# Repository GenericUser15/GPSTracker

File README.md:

# GPS Tracker

After having to cancel vet appointments because my cats were gallivanting somewhere outside, I decided to build a GPS tracking collar. These already exist but I wanted to create a fully open sourced version. I'm an embedded software engineer so my PCB knowledge is lacking, I'm much more software orientated! The PCB has been designed on KiCad.

# Architecture

The device uses a U-BLOX SARA-N310 LTE module, U-BLOX ZOE-M8G GPS module, an embedded SIM card and an STM32L011 to control everything.

The ST uses two UART lines to communicate with the GPS device and the LTE device. The GPS device will output NMEA messages by default but both lines are connected in case there is a requirement to modify any of the default settings.

The LTE device is controlled with AT commands and will communicate with the SIM card by itself.

The LTE device will then send GPS data to an endpoint, the UI can then pick up this data and overlay it on a map.

The idea is to keep everything in a deep sleep mode as much as possible, only waking to send some data. This is to reduce power consumption as much as possible. 

I'm not decided on how often to update the GPS. Maybe it can be geo-fenced so that it will update at a low rate (once a minute?) if the device hasn't left the house. Otherwise, update every 10 seconds. This will need some discussion and testing. Power consumption will come into this decision too.

# UI

I haven't given the UI much thought or how it would even work. This is something that needs to be discussed. It should have a map overlay which will plot where the cat has been over a ime period that the user can select. It should also be able to plot the current location.

# Hardware

A big consideration for this project is power usage and footprint. The smaller and lighter the PCB, the better. A small device is less likely to get stuck in something, making the collar snap free. Also, some cats may find it annoying if it's a bit bulky. The GPS and ST have been chosen for their low current draw. 

I would like to make the whole thing waterproof is possible, or at least water resistant. Who knows what crazy situations cats get into! 

I have included lots of test points but these can be removed in the final design.

# Antennas

The GPS antenna will be a small puck antenna. The device will naturally sit under a cats neck, this is going to be a problem for GPS! I don't know if the antenna will be sensitive enough to pick up GPS data bouncing off of the ground, this is something that could be tested. It this isn't an option, perhaps the whole thing could be integrated into a collar as one unit, with the antenna running up inside the collar.

I haven't given the LTE antenna much thought, it would be really nice to have it designed into the PCB but I don't know enough about antenna design to do this. The current design is for an external antenna with a UFL connection. Hopefully there is an antenna small enough to fit!

# Software

I planned to use the HAL for the ST, the software shouldn't be that complicated and using the HAL will make it much easier to get this up and running. 

There needs to be a server somewhere to provide the front end and store some historic GPS data. This should be a full stack app that can be accessed from anywhere. The front end needs a map of the world, on to which the position can be overlaid. There should be a "live" mode which just reads an endpoint, waiting for GPS data to come in and then updating the point on the map. 

The server should also store all GPS data so the user can login and plot where the device has been over a user defined period of time. This will allow the user to see where the device has been on a given day, week or longer.

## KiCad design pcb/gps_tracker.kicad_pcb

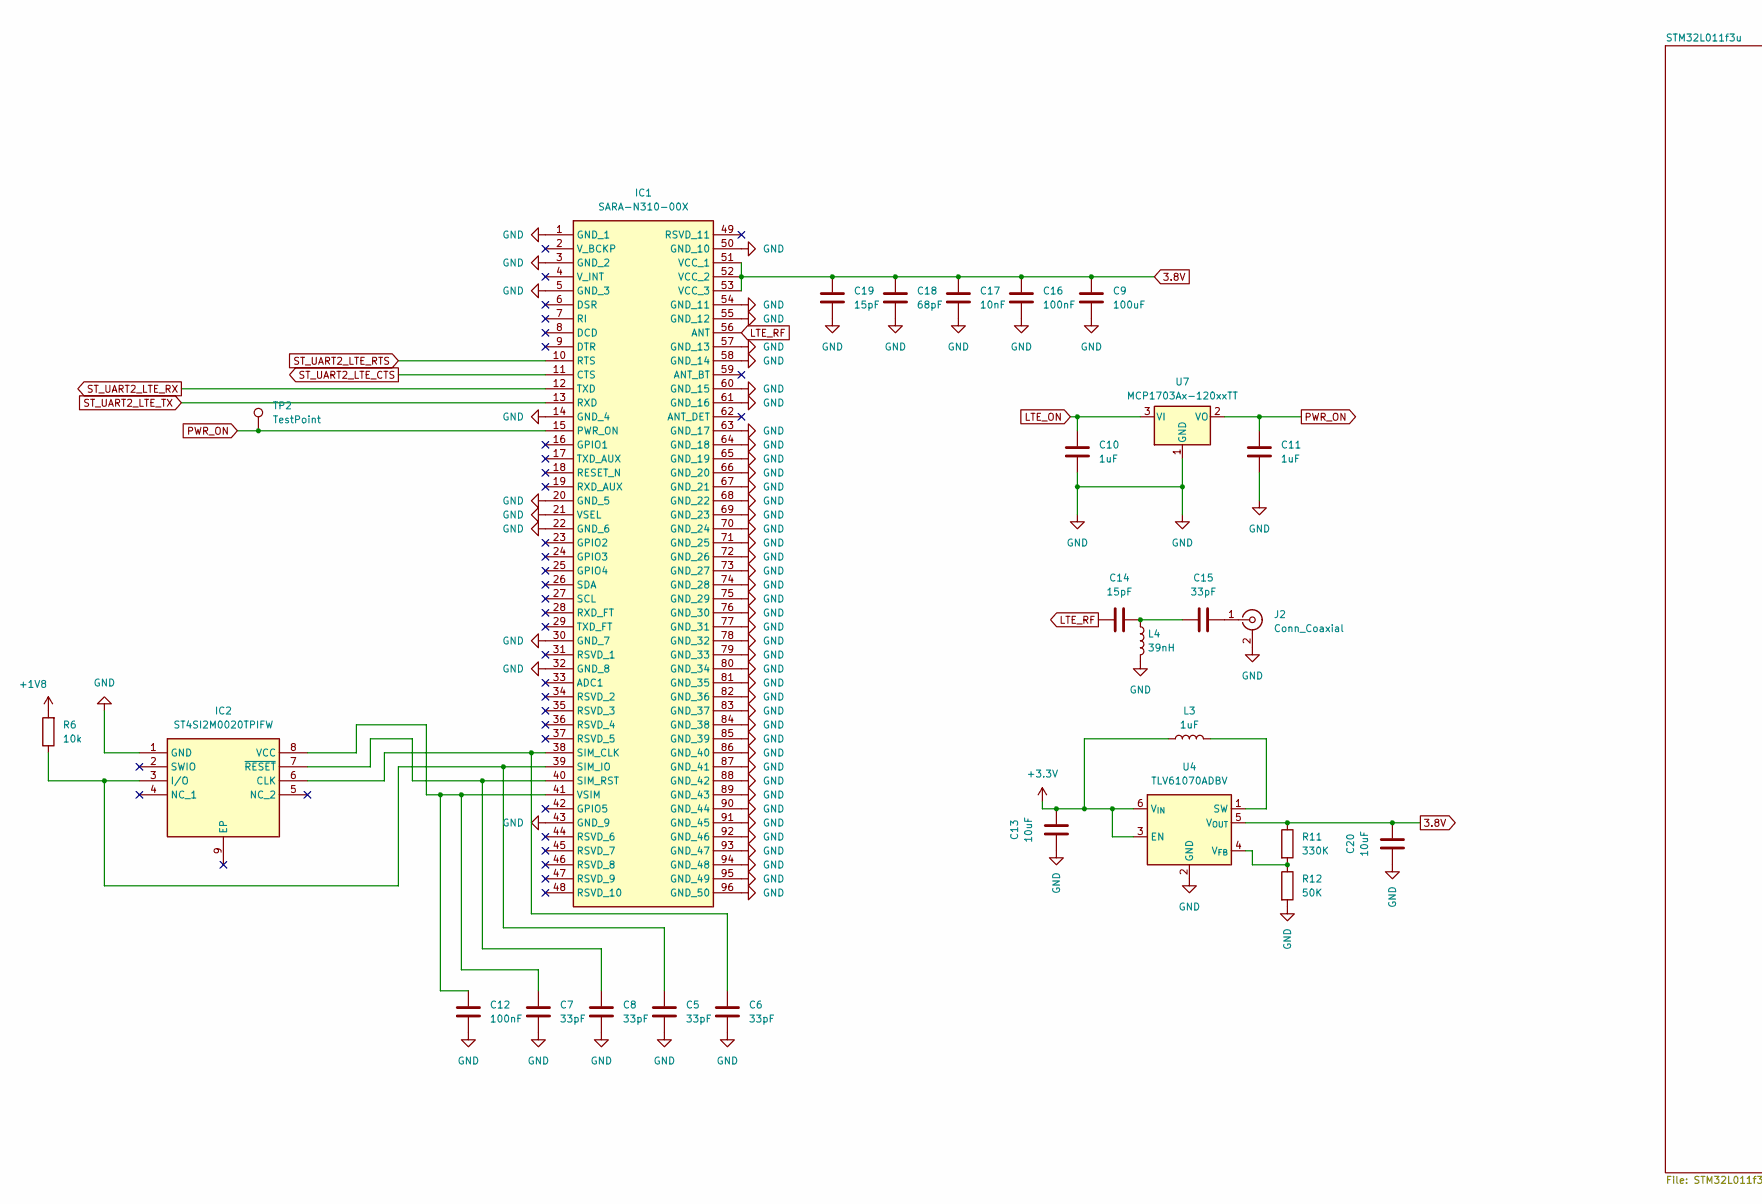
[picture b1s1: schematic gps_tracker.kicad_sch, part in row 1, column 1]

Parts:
C5, C6, C7, C8, C15: 33pF; C_01005_0402Metric_Pad0.57x0.30mm_HandSolder
C9: 100uF; C_01005_0402Metric_Pad0.57x0.30mm_HandSolder
C10, C11: 1uF; C_01005_0402Metric_Pad0.57x0.30mm_HandSolder
C12, C16: 100nF; C_01005_0402Metric_Pad0.57x0.30mm_HandSolder
C13, C20: 10uF; C_01005_0402Metric_Pad0.57x0.30mm_HandSolder
C14, C19: 15pF; C_01005_0402Metric_Pad0.57x0.30mm_HandSolder
C17: 10nF; C_01005_0402Metric_Pad0.57x0.30mm_HandSolder
C18: 68pF; C_01005_0402Metric_Pad0.57x0.30mm_HandSolder
IC1: SARA-N310-00X; SARAN31000X; Mouser Part Number 377-SARA-N310-00X
IC2: ST4SI2M0020TPIFW; SON127P600X500X100-9N; Mouser Part Number 511-ST4SI2M0020TPIFW
J2: Conn_Coaxial; U.FL_Hirose_U.FL-R-SMT-1_Vertical
L3: 1uF; L_0402_1005Metric_Pad0.77x0.64mm_HandSolder
L4: 39nH; L_0402_1005Metric_Pad0.77x0.64mm_HandSolder
R6: 10k; R_0201_0603Metric_Pad0.64x0.40mm_HandSolder
R11: 330K; R_0201_0603Metric_Pad0.64x0.40mm_HandSolder
R12: 50K; R_0201_0603Metric_Pad0.64x0.40mm_HandSolder
TP2: TestPoint; TestPoint_Pad_D1.0mm
U4: TLV61070ADBV; SOT-23-6
U7: MCP1703Ax-120xxTT; SOT-23

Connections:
3.8V: C9.1, C16.1, C17.1, C18.1, C19.1, C20.2, IC1.51 (VCC_1), IC1.52 (VCC_2), IC1.53 (VCC_3), R11.1, U4.5 (V_{OUT})
+1V8: R6.2; also elsewhere on the board
+3.3V: C13.2, L3.1, U4.3 (EN), U4.6 (V_{IN}); also elsewhere on the board
GND: C5.2, C6.2, C7.2, C8.2, C9.2, C10.2, C11.2, C12.2, C13.1, C16.2, C17.2, C18.2, C19.2, C20.1, IC1.1 (GND_1), IC1.3 (GND_2), IC1.5 (GND_3), IC1.14 (GND_4), IC1.20 (GND_5), IC1.21 (VSEL), IC1.22 (GND_6), IC1.30 (GND_7), IC1.32 (GND_8), IC1.43 (GND_9), IC1.50 (GND_10), IC1.54 (GND_11), IC1.55 (GND_12), IC1.57 (GND_13), IC1.58 (GND_14), IC1.60 (GND_15), IC1.61 (GND_16), IC1.63 (GND_17), IC1.64 (GND_18), IC1.65 (GND_19), IC1.66 (GND_20), IC1.67 (GND_21), IC1.68 (GND_22), IC1.69 (GND_23), IC1.70 (GND_24), IC1.71 (GND_25), IC1.72 (GND_26), IC1.73 (GND_27), IC1.74 (GND_28), IC1.75 (GND_29), IC1.76 (GND_30), IC1.77 (GND_31), IC1.78 (GND_32), IC1.79 (GND_33), IC1.80 (GND_34), IC1.81 (GND_35), IC1.82 (GND_36), IC1.83 (GND_37), IC1.84 (GND_38), IC1.85 (GND_39), IC1.86 (GND_40), IC1.87 (GND_41), IC1.88 (GND_42), IC1.89 (GND_43), IC1.90 (GND_44), IC1.91 (GND_45), IC1.92 (GND_46), IC1.93 (GND_47), IC1.94 (GND_48), IC1.95 (GND_49), IC1.96 (GND_50), IC2.1 (GND), J2.2 (Ext), L4.2, R12.2, U4.2 (GND), U7.1 (GND); also elsewhere on the board
LTE_ON: C10.1, U7.3 (VI); also elsewhere on the board
LTE_RF: C14.1, IC1.56 (ANT)
unnamed: C14.2, C15.1, L4.1
unnamed: C6.1, IC1.38 (SIM_CLK), IC2.6 (CLK)
unnamed: C5.1, IC1.39 (SIM_IO), IC2.3 (I/O), R6.1
unnamed: C8.1, IC1.40 (SIM_RST), IC2.7 (~RESET)
unnamed: C7.1, C12.1, IC1.41 (VSIM), IC2.8 (VCC)
unnamed: C15.2, J2.1 (In)
unnamed: L3.2, U4.1 (SW)
unnamed: R11.2, R12.1, U4.4 (V_{FB})
PWR_ON: C11.1, IC1.15 (PWR_ON), TP2.1, U7.2 (VO)
ST_UART2_LTE_CTS: IC1.11 (CTS); also elsewhere on the board
ST_UART2_LTE_RTS: IC1.10 (RTS); also elsewhere on the board
ST_UART2_LTE_RX: IC1.12 (TXD); also elsewhere on the board
ST_UART2_LTE_TX: IC1.13 (RXD); also elsewhere on the board

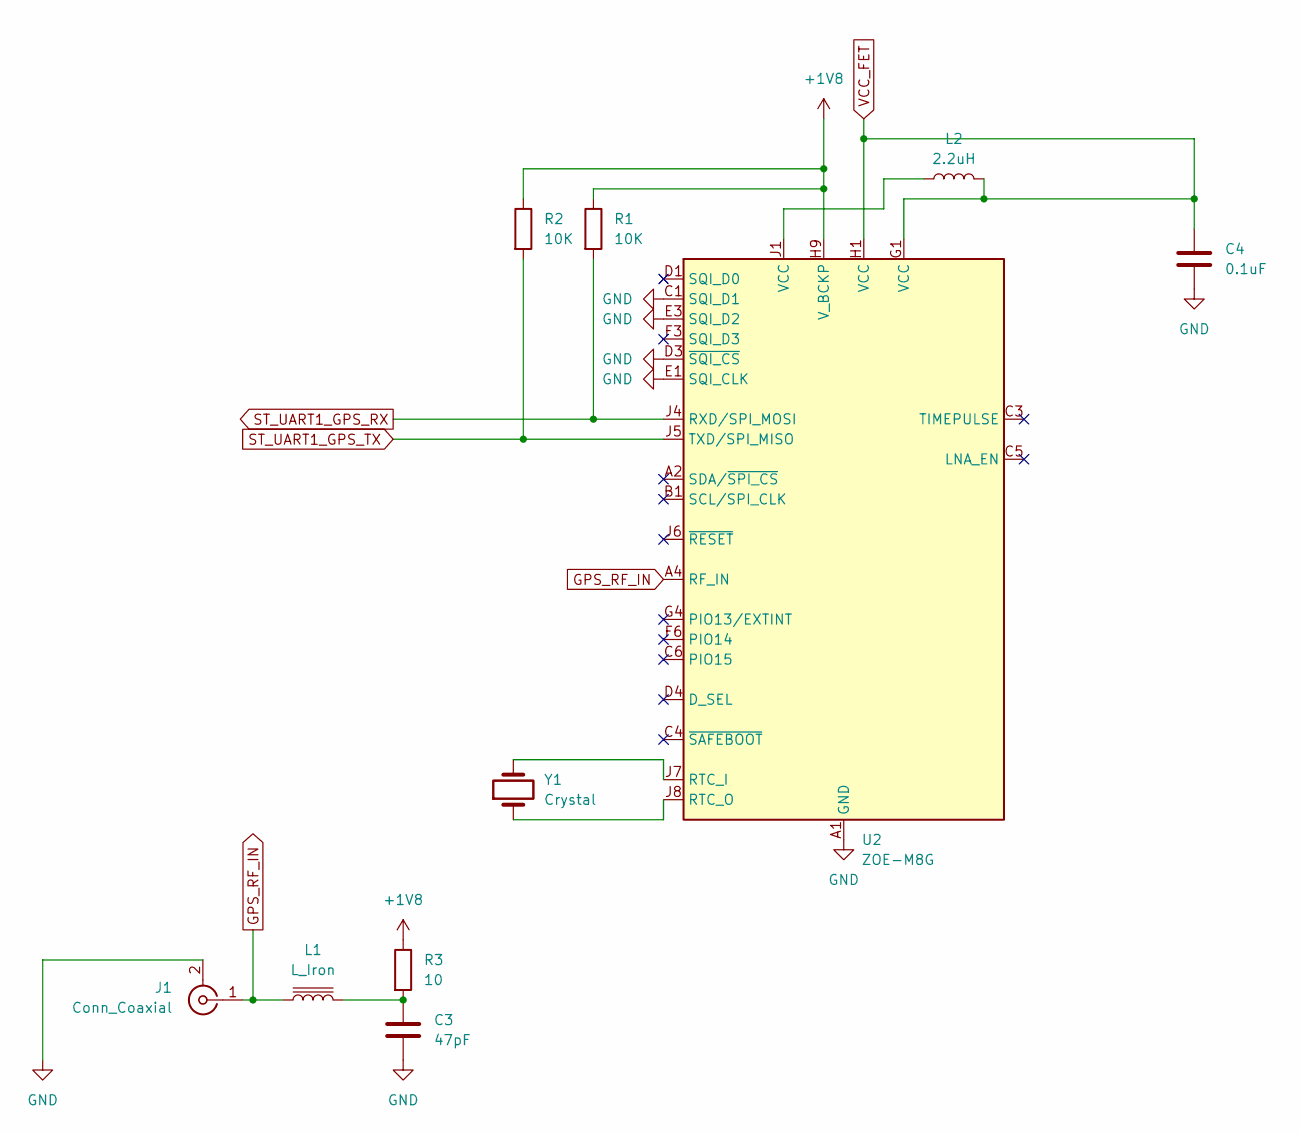
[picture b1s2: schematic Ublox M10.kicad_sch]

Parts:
C3: 47pF; C_01005_0402Metric_Pad0.57x0.30mm_HandSolder
C4: 0.1uF; C_01005_0402Metric_Pad0.57x0.30mm_HandSolder
J1: Conn_Coaxial; U.FL_Hirose_U.FL-R-SMT-1_Vertical
L1: L_Iron; L_0402_1005Metric_Pad0.77x0.64mm_HandSolder
L2: 2.2uH; L_0402_1005Metric_Pad0.77x0.64mm_HandSolder
R1, R2: 10K; R_0201_0603Metric_Pad0.64x0.40mm_HandSolder
R3: 10; R_0201_0603Metric_Pad0.64x0.40mm_HandSolder
U2: ZOE-M8G; ublox_ZOE_M8
Y1: Crystal; Crystal_SMD_MicroCrystal_CM9V-T1A-2Pin_1.6x1.0mm_HandSolder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

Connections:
+1V8: R1.1, R2.1, R3.1, U2.H9 (V_BCKP); also elsewhere on the board
GND: C3.2, C4.2, J1.2 (Ext), U2.A1 (GND), U2.A3 (GND), U2.A5 (GND), U2.A7 (GND), U2.A8 (GND), U2.A9 (GND), U2.B9 (GND), U2.C1 (SQI_D1), U2.C7 (GND), U2.C9 (GND), U2.D3 (~SQI_CS), U2.D6 (GND), U2.D9 (GND), U2.E1 (SQI_CLK), U2.E3 (SQI_D2), U2.E7 (GND), U2.F7 (GND), U2.G3 (GND), U2.G6 (GND), U2.G7 (GND), U2.J3 (GND), U2.J9 (GND); also elsewhere on the board
GPS_RF_IN: J1.1 (In), L1.1, U2.A4 (RF_IN)
unnamed: C3.1, L1.2, R3.2
unnamed: L2.1, U2.J1 (VCC), U2.J2 (VCC)
unnamed: U2.J7 (RTC_I), Y1.2
unnamed: U2.J8 (RTC_O), Y1.1
ST_UART1_GPS_RX: R1.2, U2.J4 (RXD/SPI_MOSI); also elsewhere on the board
ST_UART1_GPS_TX: R2.2, U2.J5 (TXD/SPI_MISO); also elsewhere on the board
VCC_FET: C4.1, L2.2, U2.G1 (VCC), U2.H1 (VCC); also elsewhere on the board

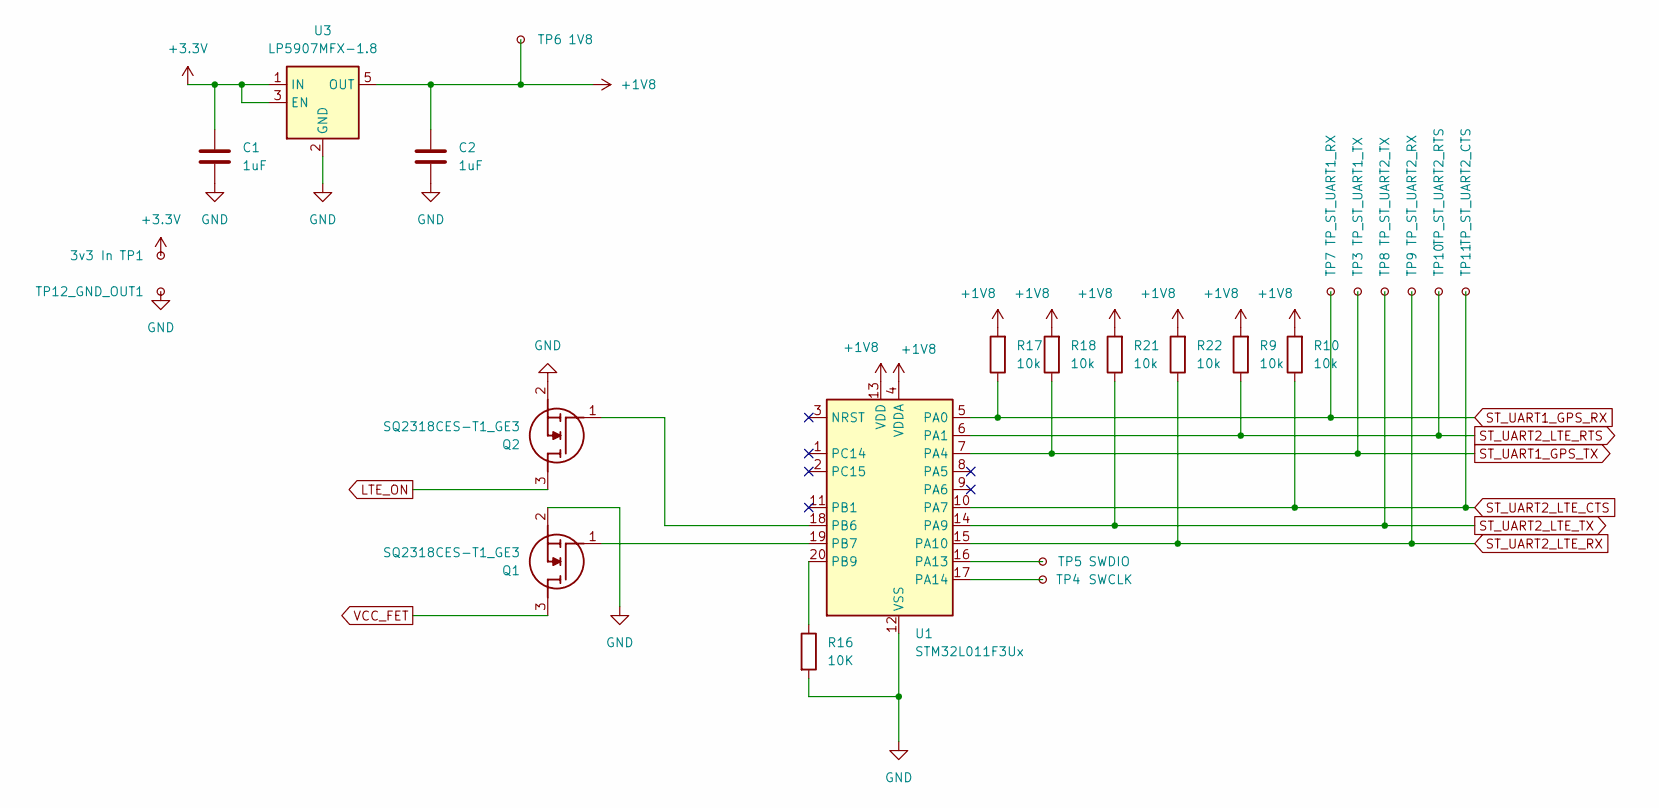
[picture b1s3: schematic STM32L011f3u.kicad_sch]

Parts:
C1, C2: 1uF; C_01005_0402Metric_Pad0.57x0.30mm_HandSolder
Q1, Q2: SQ2318CES-T1_GE3; SOT95P237X112-3N; Mouser Part Number 78-SQ2318CES-T1_GE3
R9, R10, R17, R18, R21, R22: 10k; R_0201_0603Metric_Pad0.64x0.40mm_HandSolder
R16: 10K; R_0201_0603Metric_Pad0.64x0.40mm_HandSolder
TP1, TP12_GND_OUT1: 3v3 In; TestPoint_THTPad_D1.0mm_Drill0.5mm
TP3: TP_ST_UART1_TX; TestPoint_Pad_D1.0mm
TP4: SWCLK; TestPoint_THTPad_D1.0mm_Drill0.5mm
TP5: SWDIO; TestPoint_THTPad_D1.0mm_Drill0.5mm
TP6: 1V8; TestPoint_Pad_D1.0mm
TP7: TP_ST_UART1_RX; TestPoint_Pad_D1.0mm
TP8: TP_ST_UART2_TX; TestPoint_Pad_D1.0mm
TP9: TP_ST_UART2_RX; TestPoint_Pad_D1.0mm
TP10: TP_ST_UART2_RTS; TestPoint_Pad_D1.0mm
TP11: TP_ST_UART2_CTS; TestPoint_Pad_D1.0mm
U1: STM32L011F3Ux; ST_UFQFPN-20_3x3mm_P0.5mm
U3: LP5907MFX-1.8; SOT-23-5

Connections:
+1V8: C2.1, R9.2, R10.2, R17.2, R18.2, R21.2, R22.2, TP6.1, U1.4 (VDDA), U1.13 (VDD), U3.5 (OUT); also elsewhere on the board
+3.3V: C1.1, TP1.1, U3.1 (IN), U3.3 (EN); also elsewhere on the board
GND: C1.2, C2.2, Q1.2 (S), Q2.2 (S), R16.2, TP12_GND_OUT1.1, U1.12 (VSS), U3.2 (GND); also elsewhere on the board
LTE_ON: Q2.3 (D); also elsewhere on the board
unnamed: Q1.1 (G), U1.19 (PB7)
unnamed: Q2.1 (G), U1.18 (PB6)
unnamed: TP5.1, U1.16 (PA13)
unnamed: TP4.1, U1.17 (PA14)
unnamed: R16.1, U1.20 (PB9)
ST_UART1_GPS_RX: R17.1, TP7.1, U1.5 (PA0); also elsewhere on the board
ST_UART1_GPS_TX: R18.1, TP3.1, U1.7 (PA4); also elsewhere on the board
ST_UART2_LTE_CTS: R10.1, TP11.1, U1.10 (PA7); also elsewhere on the board
ST_UART2_LTE_RTS: R9.1, TP10.1, U1.6 (PA1); also elsewhere on the board
ST_UART2_LTE_RX: R22.1, TP9.1, U1.15 (PA10); also elsewhere on the board
ST_UART2_LTE_TX: R21.1, TP8.1, U1.14 (PA9); also elsewhere on the board
VCC_FET: Q1.3 (D); also elsewhere on the board

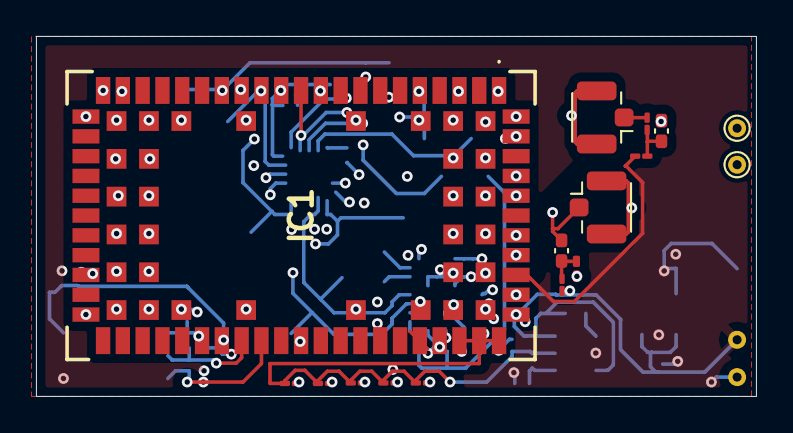
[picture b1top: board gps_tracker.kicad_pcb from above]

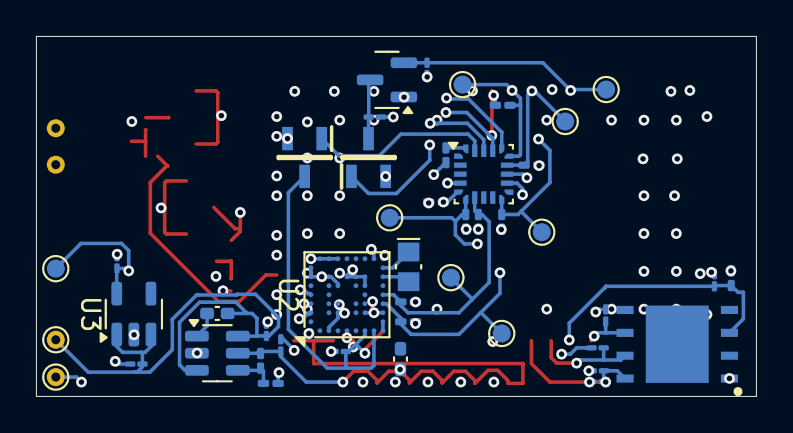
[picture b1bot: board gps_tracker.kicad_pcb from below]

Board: 6 copper layers, 40.0 x 20.0 mm, 61 parts (45 on the bottom side), 32 nets.

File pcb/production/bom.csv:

Designator,Footprint,Quantity,Value,LCSC Part #
"C1, C10, C11, C2",01005,4,1uF,
"C12, C16",01005,2,100nF,
"C13, C20",01005,2,10uF,
"C14, C19",01005,2,15pF,
"C15, C5, C6, C7, C8",01005,5,33pF,
C17,01005,1,10nF,
C18,01005,1,68pF,
C3,01005,1,47pF,
C4,01005,1,0.1uF,
C9,01005,1,100uF,
IC1,SARAN31000X,1,SARA-N310-00X,
IC2,SON127P600X500X100-9N,1,ST4SI2M0020TPIFW,
"J1, J2",U.FL_Hirose_U.FL-R-SMT-1_Vertical,2,Conn_Coaxial,
L1,0402,1,L_Iron,
L2,0402,1,2.2uH,
L3,0402,1,1uF,
L4,0402,1,39nH,
"Q1, Q2",SOT95P237X112-3N,2,SQ2318CES-T1_GE3,
"R1, R10, R16, R17, R18, R2, R21, R22, R6, R9",0201,10,10K,
R11,0201,1,330K,
R12,0201,1,50K,
R3,0201,1,10,
"TP1, TP12_GND_OUT1",TestPoint_THTPad_D1.0mm_Drill0.5mm,2,3v3 In,
TP10,TestPoint_Pad_D1.0mm,1,TP_ST_UART2_RTS,
TP11,TestPoint_Pad_D1.0mm,1,TP_ST_UART2_CTS,
TP2,TestPoint_Pad_D1.0mm,1,TestPoint,
TP3,TestPoint_Pad_D1.0mm,1,TP_ST_UART1_TX,
TP4,TestPoint_THTPad_D1.0mm_Drill0.5mm,1,SWCLK,
TP5,TestPoint_THTPad_D1.0mm_Drill0.5mm,1,SWDIO,
TP6,TestPoint_Pad_D1.0mm,1,1V8,
TP7,TestPoint_Pad_D1.0mm,1,TP_ST_UART1_RX,
TP8,TestPoint_Pad_D1.0mm,1,TP_ST_UART2_TX,
TP9,TestPoint_Pad_D1.0mm,1,TP_ST_UART2_RX,
U1,ST_UFQFPN-20_3x3mm_P0.5mm,1,STM32L011F3Ux,
U2,ublox_ZOE_M8,1,ZOE-M8G,
U3,SOT-23-5,1,LP5907MFX-1.8,
U4,SOT-23-6,1,TLV61070ADBV,
U7,SOT-23,1,MCP1703Ax-120xxTT,
Y1,Crystal_SMD_MicroCrystal_CM9V-T1A-2Pin_1.6x1.0mm_HandSoldering,1,Crystal,

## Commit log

2025-01-04 moved to pcb to own dir
2025-01-04 Create LICENSE
